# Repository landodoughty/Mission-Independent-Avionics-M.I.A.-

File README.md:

# Mission-Independent-Avionics-M.I.A.-
My Custom Rocket Avionics System

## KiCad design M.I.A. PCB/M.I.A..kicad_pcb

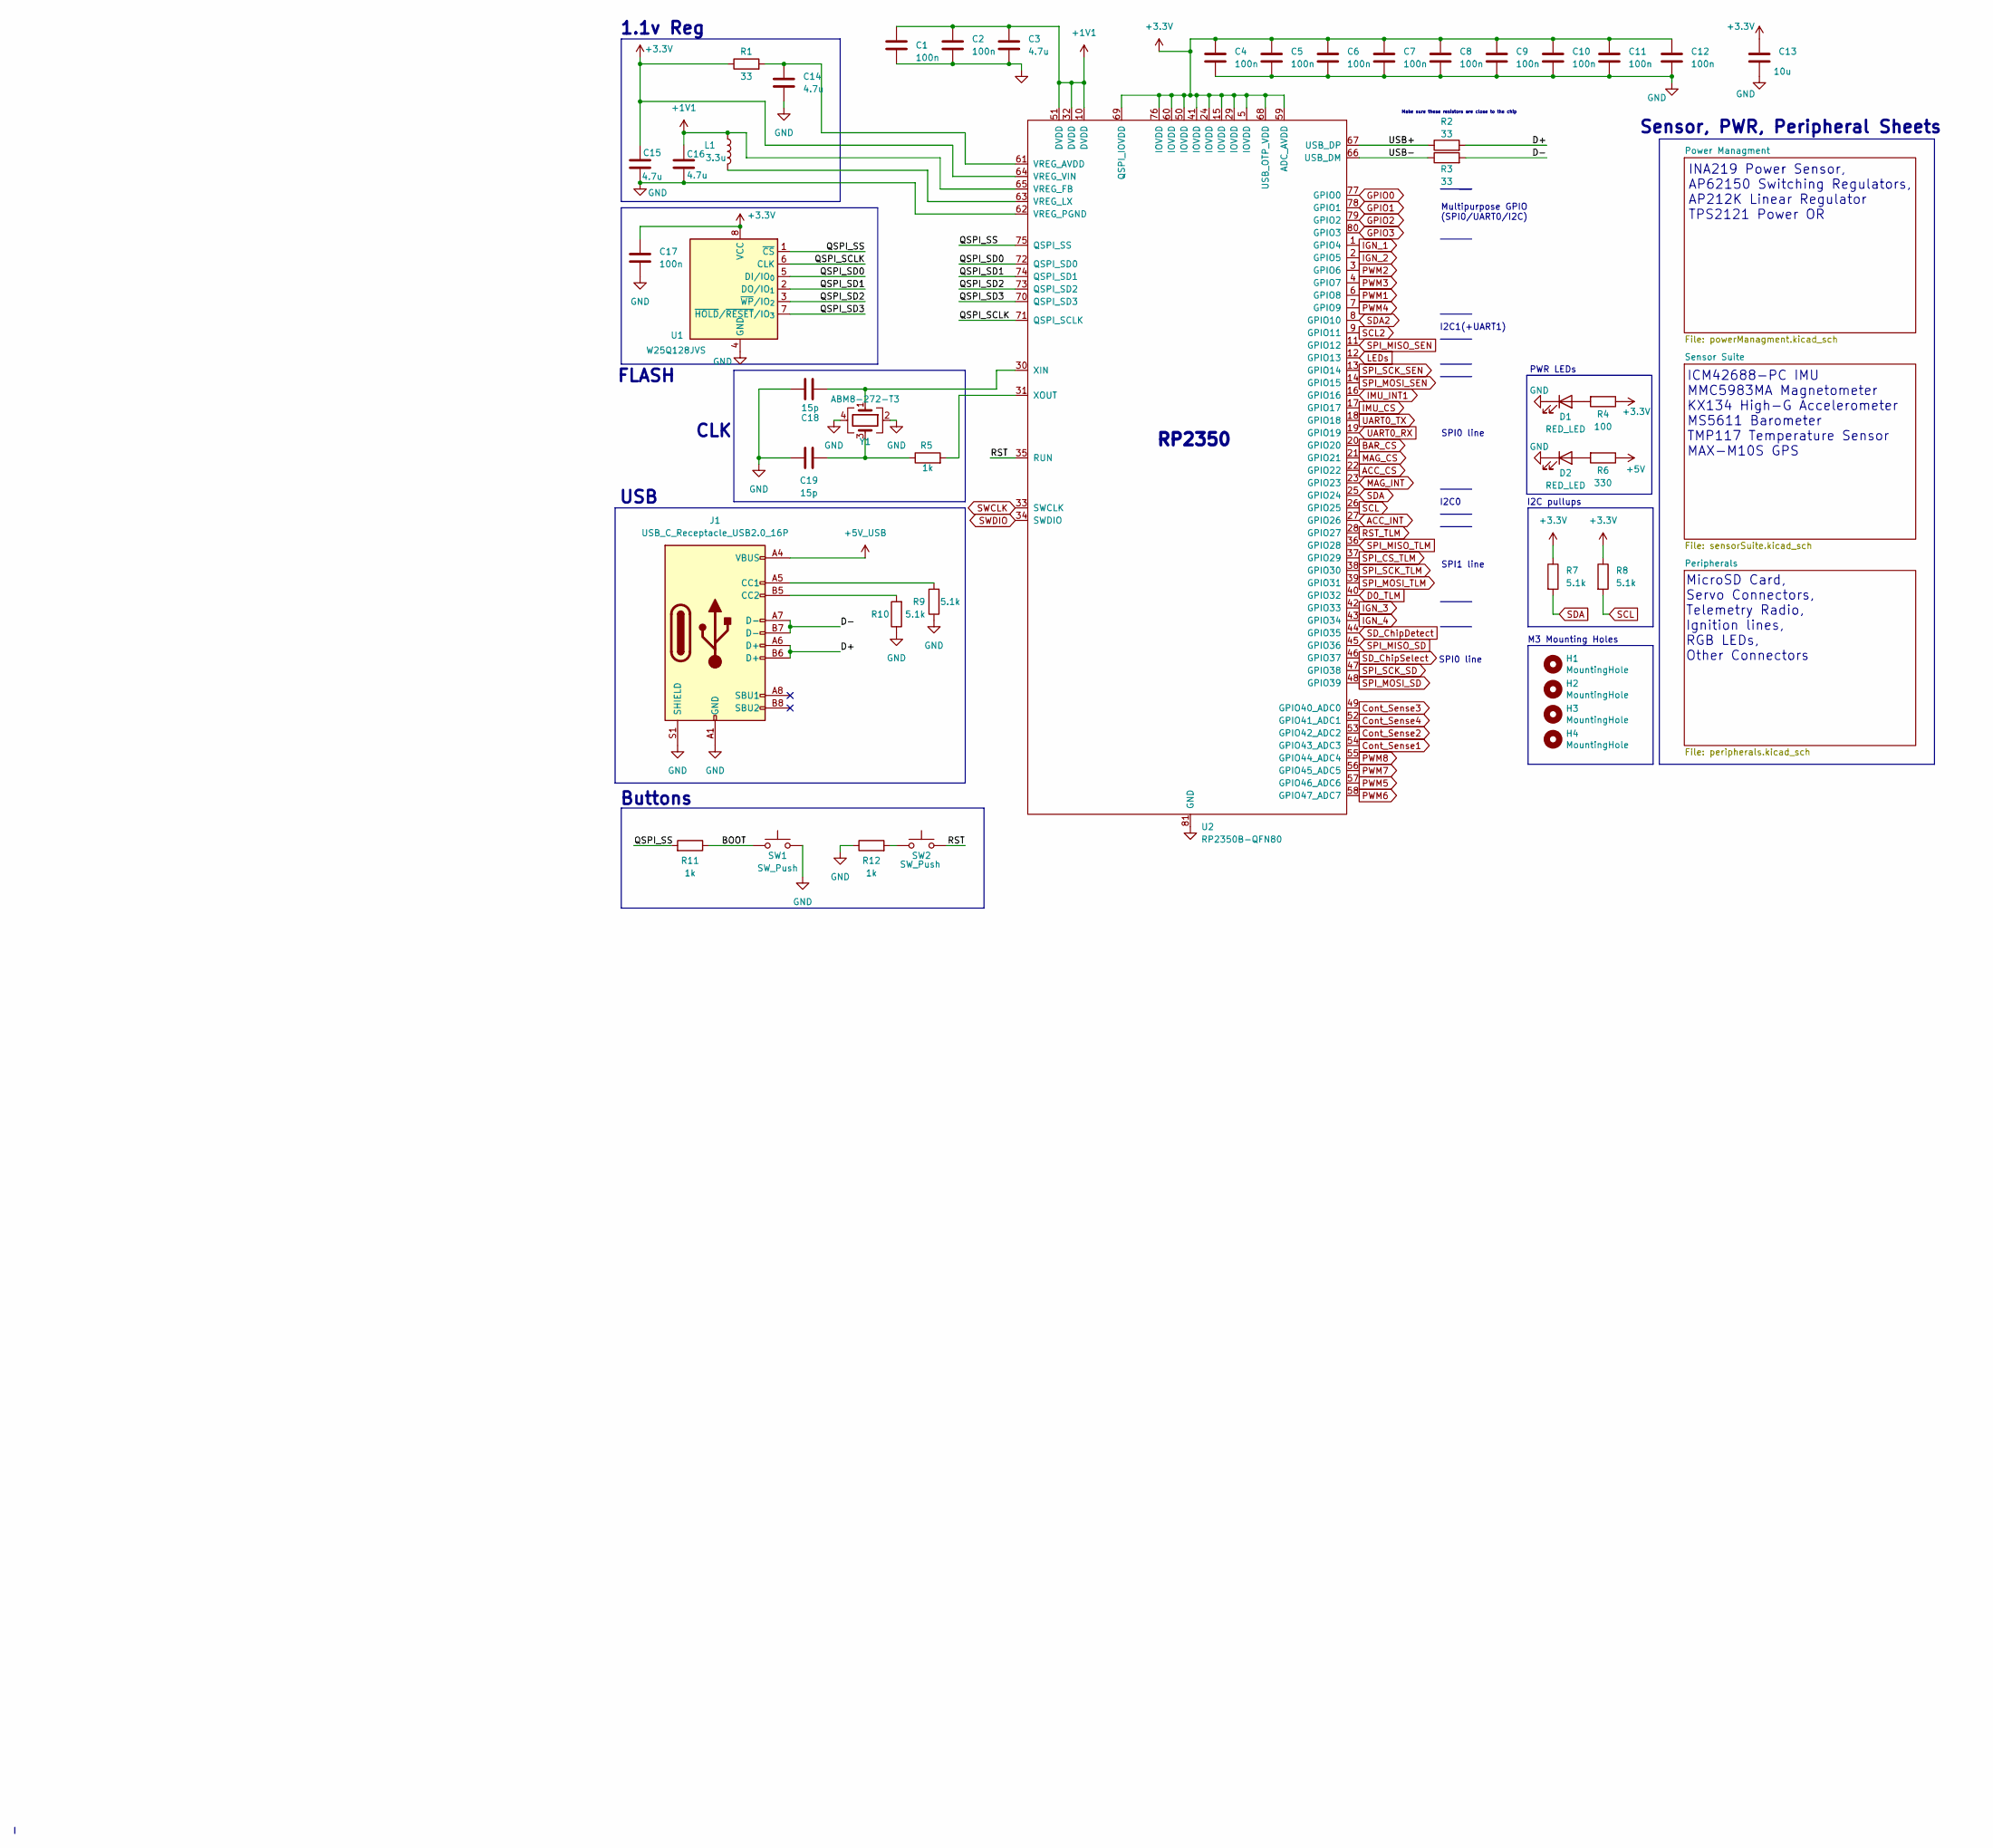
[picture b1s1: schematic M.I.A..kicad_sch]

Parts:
C1, C2, C4, C5, C6, C7, C8, C9, C10, C11, C12, C17: 100n; C_0603_1608Metric; LCSC Part Number C1525
C3, C14, C15, C16: 4.7u; C_0805_2012Metric; LCSC Part Number C23733
C13: 10u; C_0805_2012Metric; LCSC Part Number C15850
C18, C19: 15p; C_0603_1608Metric; LCSC Part Number C1548
D1, D2: RED_LED; LED_0805_2012Metric; LCSC Part Number C84256
H1, H2, H3, H4: MountingHole; MountingHole_3.2mm_M3_ISO14580_Pad
J1: USB_C_Receptacle_USB2.0_16P; USB_C_Receptacle_HRO_TYPE-C-31-M-12
L1: 3.3u; AOTA-B201610S3R3-101-T(L_0806_2016metric)
R1: 33; R_0603_1608Metric; LCSC Part Number C25105
R2, R3: 33; R_0603_1608Metric; LCSC Part Number C25092
R4: 100; R_0603_1608Metric; LCSC Part Number C25076
R5, R11, R12: 1k; R_0603_1608Metric; LCSC Part Number C11702
R6: 330; R_0603_1608Metric; LCSC Part Number C25076
R7, R8: 5.1k; R_0603_1608Metric; LCSC Part Number C25900
R9, R10: 5.1k; R_0603_1608Metric; LCSC Part Number C25105
SW1, SW2: SW_Push; SW_Push_SPST_NO_Alps_SKRK
U1: W25Q128JVS; WSON-8-1EP_6x5mm_P1.27mm_EP3.4x4mm; LCSC Part Number C97521
U2: RP2350B-QFN80; QFN-80-1EP_10x10mm_P0.4mm_EP3.4x3.4mm
Y1: ABM8-272-T3; Crystal_SMD_3225-4Pin_3.2x2.5mm; LCSC Part Number C20625731

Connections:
+1V1: C1.1, C2.1, C3.1, C16.1, L1.1, U2.10 (DVDD), U2.32 (DVDD), U2.51 (DVDD), U2.65 (VREG_FB)
+3.3V: C4.1, C5.1, C6.1, C7.1, C8.1, C9.1, C10.1, C11.1, C12.1, C13.1, C15.1, C17.1, R1.1, R4.1, R7.1, R8.1, U1.8 (VCC), U2.5 (IOVDD), U2.15 (IOVDD), U2.24 (IOVDD), U2.29 (IOVDD), U2.41 (IOVDD), U2.50 (IOVDD), U2.59 (ADC_AVDD), U2.60 (IOVDD), U2.64 (VREG_VIN), U2.68 (USB_OTP_VDD), U2.69 (QSPI_IOVDD), U2.76 (IOVDD); also elsewhere on the board
+5V: R6.1; also elsewhere on the board
+5V_USB: J1.A4 (VBUS), J1.A9 (VBUS), J1.B4 (VBUS), J1.B9 (VBUS); also elsewhere on the board
/BOOT: R11.1, SW1.2
/D+: J1.A6 (D+), J1.B6 (D+), R2.2
/D-: J1.A7 (D-), J1.B7 (D-), R3.2
/QSPI_SCLK: U1.6 (CLK), U2.71 (QSPI_SCLK)
/QSPI_SD0: U1.5 (DI/IO_{0}), U2.72 (QSPI_SD0)
/QSPI_SD1: U1.2 (DO/IO_{1}), U2.74 (QSPI_SD1)
/QSPI_SD2: U1.3 (~WP/IO_{2}), U2.73 (QSPI_SD2)
/QSPI_SD3: U1.7 (~HOLD/~RESET/IO_{3}), U2.70 (QSPI_SD3)
/QSPI_SS: R11.2, U1.1 (~CS), U2.75 (QSPI_SS)
/RST: SW2.2, U2.35 (RUN)
/USB+: R2.1, U2.67 (USB_DP)
/USB-: R3.1, U2.66 (USB_DM)
ACC_CS: U2.22 (GPIO22); also elsewhere on the board
ACC_INT: U2.27 (GPIO26); also elsewhere on the board
BAR_CS: U2.20 (GPIO20); also elsewhere on the board
Cont_Sense1: U2.54 (GPIO43_ADC3); also elsewhere on the board
Cont_Sense2: U2.53 (GPIO42_ADC2); also elsewhere on the board
Cont_Sense3: U2.49 (GPIO40_ADC0); also elsewhere on the board
Cont_Sense4: U2.52 (GPIO41_ADC1); also elsewhere on the board
D0_TLM: U2.40 (GPIO32); also elsewhere on the board
GND: C1.2, C2.2, C3.2, C4.2, C5.2, C6.2, C7.2, C8.2, C9.2, C10.2, C11.2, C12.2, C13.2, C14.2, C15.2, C16.2, C17.2, C18.1, C19.1, D1.1 (K), D2.1 (K), J1.A1 (GND), J1.A12 (GND), J1.B1 (GND), J1.B12 (GND), J1.S1 (SHIELD), R9.1, R10.1, R12.1, SW1.1, U1.4 (GND), U2.62 (VREG_PGND), U2.81 (GND), Y1.2, Y1.4; also elsewhere on the board
GPIO0: U2.77 (GPIO0); also elsewhere on the board
GPIO1: U2.78 (GPIO1); also elsewhere on the board
GPIO2: U2.79 (GPIO2); also elsewhere on the board
GPIO3: U2.80 (GPIO3); also elsewhere on the board
IGN_1: U2.1 (GPIO4); also elsewhere on the board
IGN_2: U2.2 (GPIO5); also elsewhere on the board
IGN_3: U2.42 (GPIO33); also elsewhere on the board
IGN_4: U2.43 (GPIO34); also elsewhere on the board
IMU_CS: U2.17 (GPIO17); also elsewhere on the board
IMU_INT1: U2.16 (GPIO16); also elsewhere on the board
LEDs: U2.12 (GPIO13); also elsewhere on the board
MAG_CS: U2.21 (GPIO21); also elsewhere on the board
MAG_INT: U2.23 (GPIO23); also elsewhere on the board
unnamed: C19.2, R5.1, Y1.3
unnamed: D1.2 (A), R4.2
unnamed: D2.2 (A), R6.2
unnamed: J1.A5 (CC1), R9.2
unnamed: J1.B5 (CC2), R10.2
unnamed: R12.2, SW2.1
unnamed: C14.1, R1.2, U2.61 (VREG_AVDD)
unnamed: L1.2, U2.63 (VREG_LX)
unnamed: C18.2, U2.30 (XIN), Y1.1
unnamed: R5.2, U2.31 (XOUT)
PWM1: U2.6 (GPIO8); also elsewhere on the board
PWM2: U2.3 (GPIO6); also elsewhere on the board
PWM3: U2.4 (GPIO7); also elsewhere on the board
PWM4: U2.7 (GPIO9); also elsewhere on the board
PWM5: U2.57 (GPIO46_ADC6); also elsewhere on the board
PWM6: U2.58 (GPIO47_ADC7); also elsewhere on the board
PWM7: U2.56 (GPIO45_ADC5); also elsewhere on the board
PWM8: U2.55 (GPIO44_ADC4); also elsewhere on the board
RST_TLM: U2.28 (GPIO27); also elsewhere on the board
SCL: R8.2, U2.26 (GPIO25); also elsewhere on the board
SCL2: U2.9 (GPIO11); also elsewhere on the board
SDA: R7.2, U2.25 (GPIO24); also elsewhere on the board
SDA2: U2.8 (GPIO10); also elsewhere on the board
SD_ChipDetect: U2.44 (GPIO35); also elsewhere on the board
SD_ChipSelect: U2.46 (GPIO37); also elsewhere on the board
SPI_CS_TLM: U2.37 (GPIO29); also elsewhere on the board
SPI_MISO_SD: U2.45 (GPIO36); also elsewhere on the board
SPI_MISO_SEN: U2.11 (GPIO12); also elsewhere on the board
SPI_MISO_TLM: U2.36 (GPIO28); also elsewhere on the board
SPI_MOSI_SD: U2.48 (GPIO39); also elsewhere on the board
SPI_MOSI_SEN: U2.14 (GPIO15); also elsewhere on the board
SPI_MOSI_TLM: U2.39 (GPIO31); also elsewhere on the board
SPI_SCK_SD: U2.47 (GPIO38); also elsewhere on the board
SPI_SCK_SEN: U2.13 (GPIO14); also elsewhere on the board
SPI_SCK_TLM: U2.38 (GPIO30); also elsewhere on the board
SWCLK: U2.33 (SWCLK); also elsewhere on the board
SWDIO: U2.34 (SWDIO); also elsewhere on the board
UART0_RX: U2.19 (GPIO19); also elsewhere on the board
UART0_TX: U2.18 (GPIO18); also elsewhere on the board

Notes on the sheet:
FLASH
Buttons
I2C0
I2C1(+UART1)
I2C pullups
SPI0 line
SPI1 line
MicroSD Card, Servo Connectors, Telemetry Radio, Ignition lines, RGB LEDs, Other Connectors
Make sure these resistors are close to the chip
USB
ICM42688-PC IMU MMC5983MA Magnetometer KX134 High-G Accelerometer MS5611 Barometer TMP117 Temperature Sensor MAX-M10S GPS
Multipurpose GPIO (SPI0/UART0/I2C)
1.1v Reg
INA219 Power Sensor, AP62150 Switching Regulators, AP212K Linear Regulator TPS2121 Power OR
CLK
PWR LEDs
RP2350
M3 Mounting Holes
Sensor, PWR, Peripheral Sheets

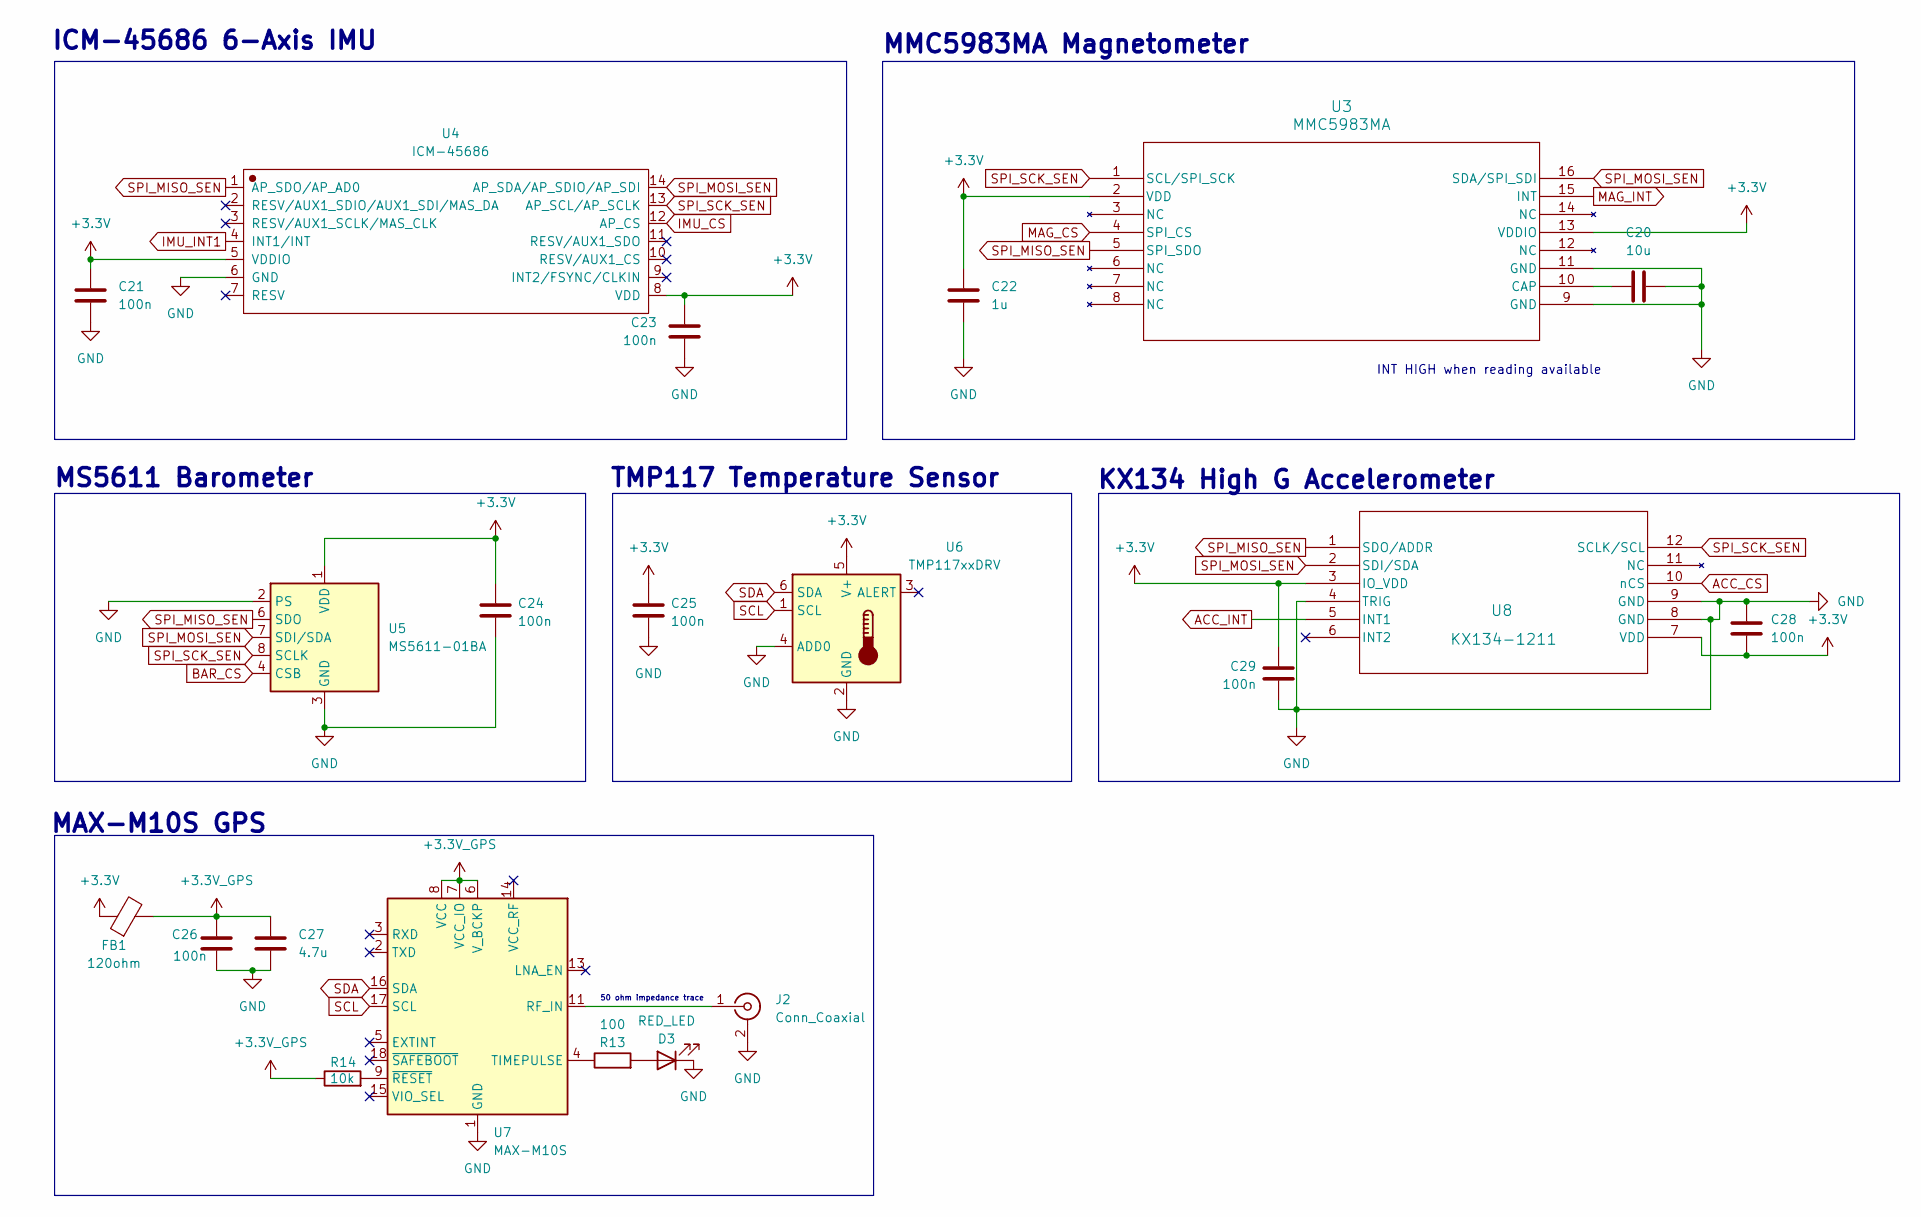
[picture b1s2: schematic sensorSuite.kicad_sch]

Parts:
C20: 10u; C_0805_2012Metric; LCSC Part Number C15850
C21, C23, C24, C25, C26, C28, C29: 100n; C_0603_1608Metric; LCSC Part Number C1525
C22: 1u; C_0805_2012Metric; LCSC Part Number C28323
C27: 4.7u; C_0805_2012Metric; LCSC Part Number C23733
D3: RED_LED; LED_0805_2012Metric; LCSC Part Number C84256
FB1: 120ohm; L_0805_2012Metric
J2: Conn_Coaxial; SMA_Amphenol_132134-11_Vertical
R13: 100; R_0603_1608Metric; LCSC Part Number C25076
R14: 10k; R_0603_1608Metric; LCSC Part Number C25744
U3: MMC5983MA; LGA-16_3x3mm_P0.5mm; LCSC Part Number C404329
U4: ICM-45686; Bosch_LGA-14_3x2.5mm_P0.5mm; Manufacturer Part ICM-45686; LCSC C22459454
U5: MS5611-01BA; LGA-8_3x5mm_P1.25mm; LCSC Part Number C15639
U6: TMP117xxDRV; WSON-6-1EP_2x2mm_P0.65mm_EP1x1.6mm
U7: MAX-M10S; ublox_MAX
U8: KX134-1211; LGA-12_2x2mm_P0.5mm; LCSC Part Number C2157908

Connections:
+3.3V: C21.1, C22.2, C23.1, C24.1, C25.1, C28.2, C29.1, FB1.1, U3.2 (VDD), U3.13 (VDDIO), U4.5 (VDDIO), U4.8 (VDD), U5.1 (VDD), U6.5 (V+), U8.3 (IO_VDD), U8.7 (VDD); also elsewhere on the board
+3.3V_GPS: C26.1, C27.1, FB1.2, R14.1, U7.6 (V_BCKP), U7.7 (VCC_IO), U7.8 (VCC)
ACC_CS: U8.10 (nCS); also elsewhere on the board
ACC_INT: U8.5 (INT1); also elsewhere on the board
BAR_CS: U5.4 (CSB), U5.5 (CSB); also elsewhere on the board
GND: C20.2, C21.2, C22.1, C23.2, C24.2, C25.2, C26.2, C27.2, C28.1, C29.2, D3.1 (K), J2.2 (Ext), U3.9 (GND), U3.11 (GND), U4.6 (GND), U5.2 (PS), U5.3 (GND), U6.2 (GND), U6.4 (ADD0), U7.1 (GND), U7.10 (GND), U7.12 (GND), U8.4 (TRIG), U8.8 (GND), U8.9 (GND); also elsewhere on the board
IMU_CS: U4.12 (AP_CS); also elsewhere on the board
IMU_INT1: U4.4 (INT1/INT); also elsewhere on the board
MAG_CS: U3.4 (SPI_CS); also elsewhere on the board
MAG_INT: U3.15 (INT); also elsewhere on the board
unnamed: D3.2 (A), R13.2
unnamed: J2.1 (In), U7.11 (RF_IN)
unnamed: C20.1, U3.10 (CAP)
unnamed: R13.1, U7.4 (TIMEPULSE)
unnamed: R14.2, U7.9 (~RESET)
SCL: U6.1 (SCL), U7.17 (SCL); also elsewhere on the board
SDA: U6.6 (SDA), U7.16 (SDA); also elsewhere on the board
SPI_MISO_SEN: U3.5 (SPI_SDO), U4.1 (AP_SDO/AP_AD0), U5.6 (SDO), U8.1 (SDO/ADDR); also elsewhere on the board
SPI_MOSI_SEN: U3.16 (SDA/SPI_SDI), U4.14 (AP_SDA/AP_SDIO/AP_SDI), U5.7 (SDI/SDA), U8.2 (SDI/SDA); also elsewhere on the board
SPI_SCK_SEN: U3.1 (SCL/SPI_SCK), U4.13 (AP_SCL/AP_SCLK), U5.8 (SCLK), U8.12 (SCLK/SCL); also elsewhere on the board

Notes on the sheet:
MMC5983MA Magnetometer
MS5611 Barometer
INT HIGH when reading available
ICM-45686 6-Axis IMU
TMP117 Temperature Sensor
KX134 High G Accelerometer
MAX-M10S GPS
50 ohm impedance trace

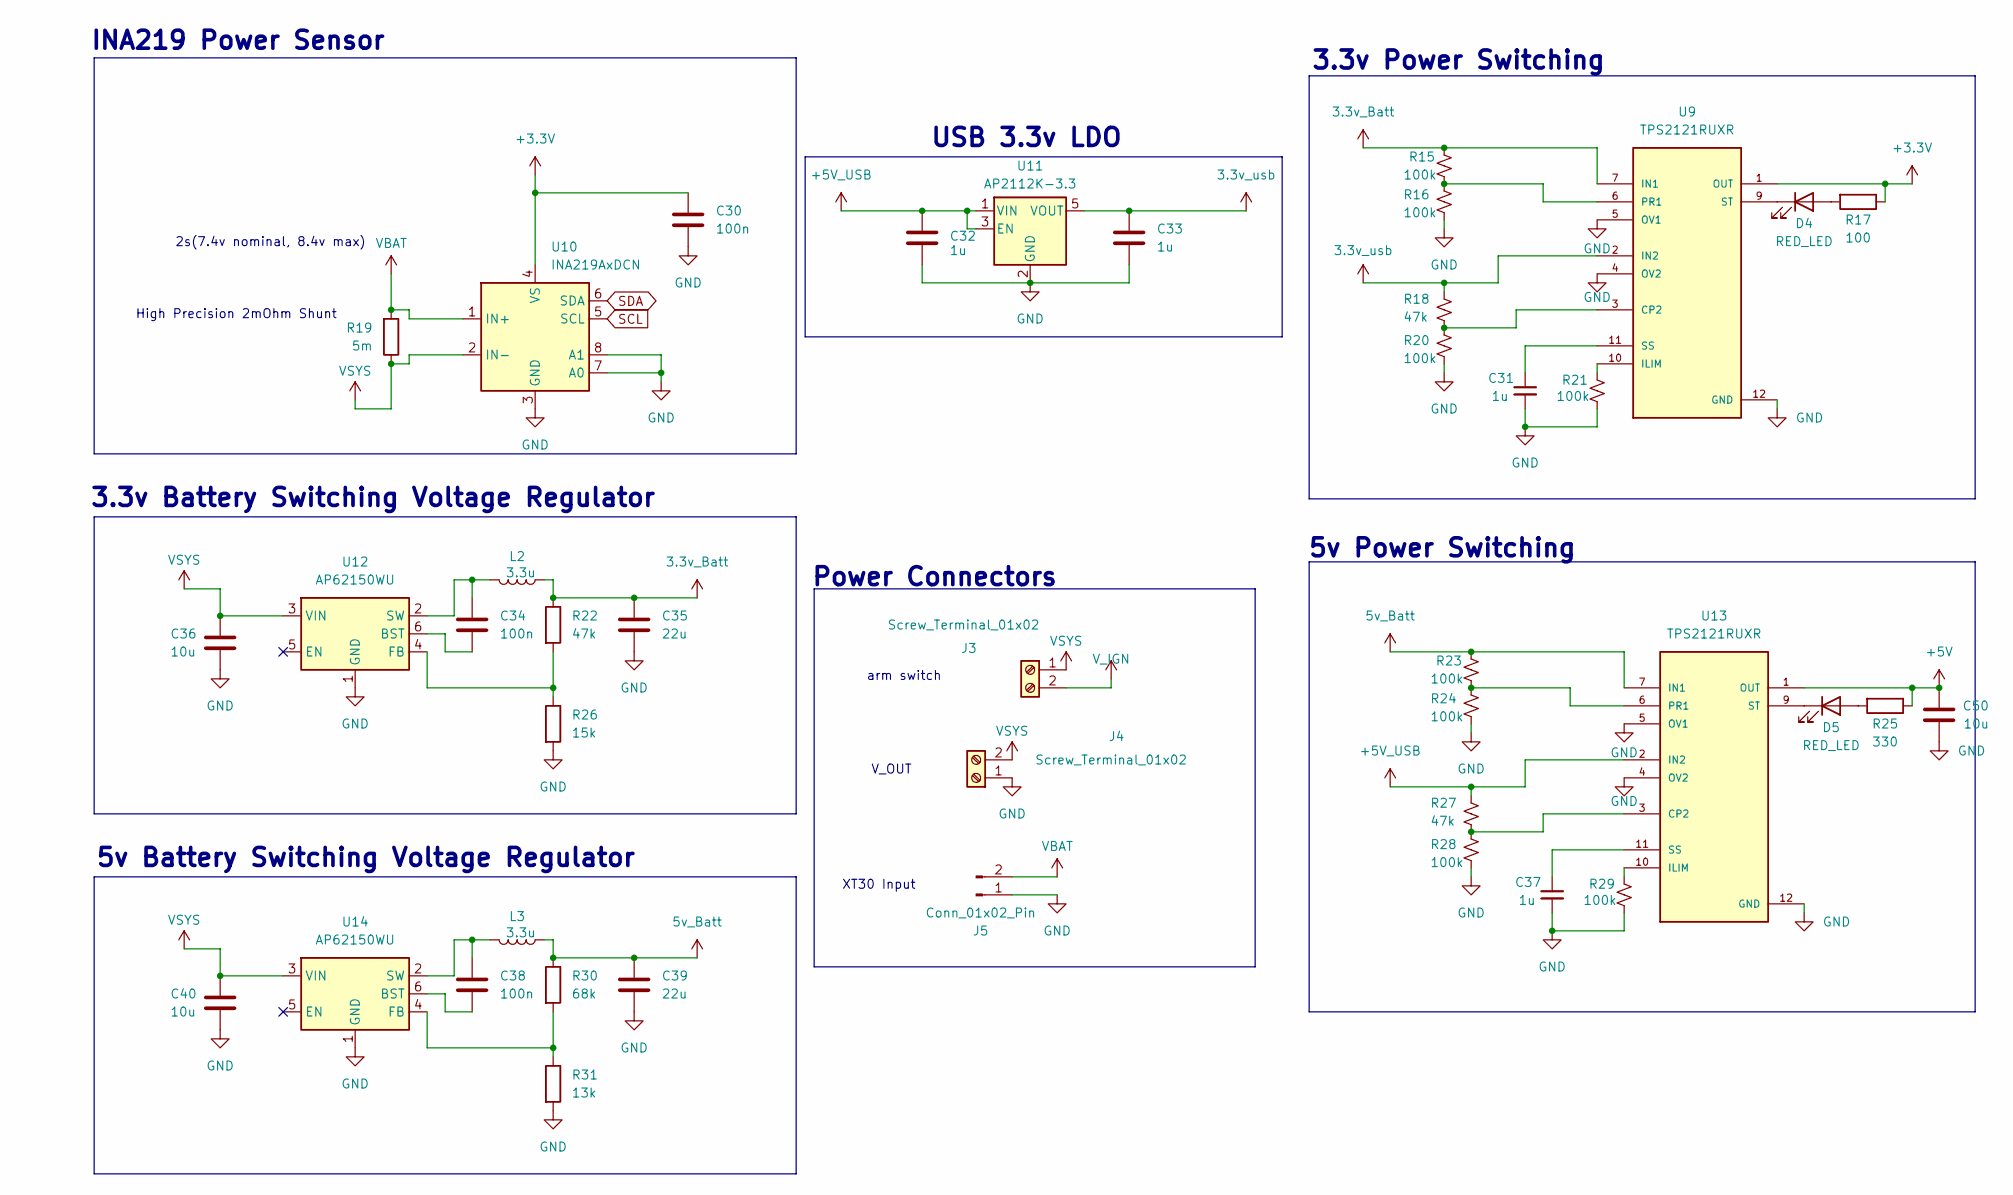
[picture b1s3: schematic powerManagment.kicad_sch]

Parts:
C30, C34, C38: 100n; C_0603_1608Metric; LCSC Part Number C1525
C31, C37: 1u; C_0805_2012Metric; LCSC Part Number C28323
C32, C33: 1u; C_0805_2012Metric; LCSC Part Number C15850
C35, C39: 22u; C_0805_2012Metric; LCSC Part Number C45783
C36, C40, C50: 10u; C_0805_2012Metric; JLCPCB Part # C15850
D4, D5: RED_LED; LED_0805_2012Metric; LCSC Part Number C84256
J3, J4: Screw_Terminal_01x02; ScrewTerminal_1x02_P3.5mm_Horizontal_Black
J5: Conn_01x02_Pin; AMASS_XT30PW-M_1x02_P2.50mm_Horizontal
L2, L3: 3.3u; AOTA-B201610S3R3-101-T(L_0806_2016metric)
R15, R23: 100k; R_0603_1608Metric; LCSC Part Number C25792
R16, R20, R21, R24, R28, R29: 100k; R_0603_1608Metric; LCSC Part Number C25741
R17: 100; R_0603_1608Metric; LCSC Part Number C25076
R18, R27: 47k; R_0603_1608Metric; LCSC Part Number C25741
R19: 5m; R_1206_3216Metric
R22: 47k; R_0603_1608Metric; LCSC Part Number C25792
R25: 330; R_0603_1608Metric; LCSC Part Number C25076
R26: 15k; R_0603_1608Metric; LCSC Part Number C25756
R30: 68k; R_0603_1608Metric; LCSC Part Number C25792
R31: 13k; R_0603_1608Metric; LCSC Part Number C25756
U9, U13: TPS2121RUXR; Texas_VQFN-HR-12_2x2.5mm_P0.5mm; LCSC Part Number C485916
U10: INA219AxDCN; SOT-23-8
U11: AP2112K-3.3; SOT-23-5
U12, U14: AP62150WU; TSOT-23-6; LCSC Part Number C3194237

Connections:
3.3v_Batt: C35.1, L2.1, R15.1, R22.1, U9.7 (IN1)
3.3v_usb: C33.1, R18.1, U9.2 (IN2), U11.5 (VOUT)
5v_Batt: C39.1, L3.1, R23.1, R30.1, U13.7 (IN1)
+3.3V: C30.1, R17.1, U9.1 (OUT), U9.8 (OUT), U10.4 (VS); also elsewhere on the board
+5V: C50.1, R25.1, U13.1 (OUT), U13.8 (OUT); also elsewhere on the board
+5V_USB: C32.1, R27.1, U11.1 (VIN), U11.3 (EN), U13.2 (IN2); also elsewhere on the board
GND: C30.2, C31.2, C32.2, C33.2, C35.2, C36.2, C37.2, C39.2, C40.2, C50.2, J4.1, J5.1, R16.2, R20.2, R21.2, R24.2, R26.2, R28.2, R29.2, R31.2, U9.4 (OV2), U9.5 (OV1), U9.12 (GND), U10.3 (GND), U10.7 (A0), U10.8 (A1), U11.2 (GND), U12.1 (GND), U13.4 (OV2), U13.5 (OV1), U13.12 (GND), U14.1 (GND); also elsewhere on the board
unnamed: D4.2 (A), R17.2
unnamed: D4.1 (K), U9.9 (ST)
unnamed: D5.2 (A), R25.2
unnamed: D5.1 (K), U13.9 (ST)
unnamed: R18.2, R20.1, U9.3 (CP2)
unnamed: R21.1, U9.10 (ILIM)
unnamed: R15.2, R16.1, U9.6 (PR1)
unnamed: C31.1, U9.11 (SS)
unnamed: C34.2, U12.6 (BST)
unnamed: R22.2, R26.1, U12.4 (FB)
unnamed: C34.1, L2.2, U12.2 (SW)
unnamed: R27.2, R28.1, U13.3 (CP2)
unnamed: R29.1, U13.10 (ILIM)
unnamed: R23.2, R24.1, U13.6 (PR1)
unnamed: C37.1, U13.11 (SS)
unnamed: C38.2, U14.6 (BST)
unnamed: R30.2, R31.1, U14.4 (FB)
unnamed: C38.1, L3.2, U14.2 (SW)
SCL: U10.5 (SCL); also elsewhere on the board
SDA: U10.6 (SDA); also elsewhere on the board
VBAT: J5.2, R19.2, U10.1 (IN+)
VSYS: C36.1, C40.1, J3.1, J4.2, R19.1, U10.2 (IN-), U12.3 (VIN), U14.3 (VIN); also elsewhere on the board
V_IGN: J3.2; also elsewhere on the board

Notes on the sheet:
Power Connectors
3.3v Battery Switching Voltage Regulator
5v Power Switching
arm switch
3.3v Power Switching
V_OUT
INA219 Power Sensor
XT30 Input
5v Battery Switching Voltage Regulator
2s(7.4v nominal, 8.4v max)
USB 3.3v LDO
High Precision 2mOhm Shunt

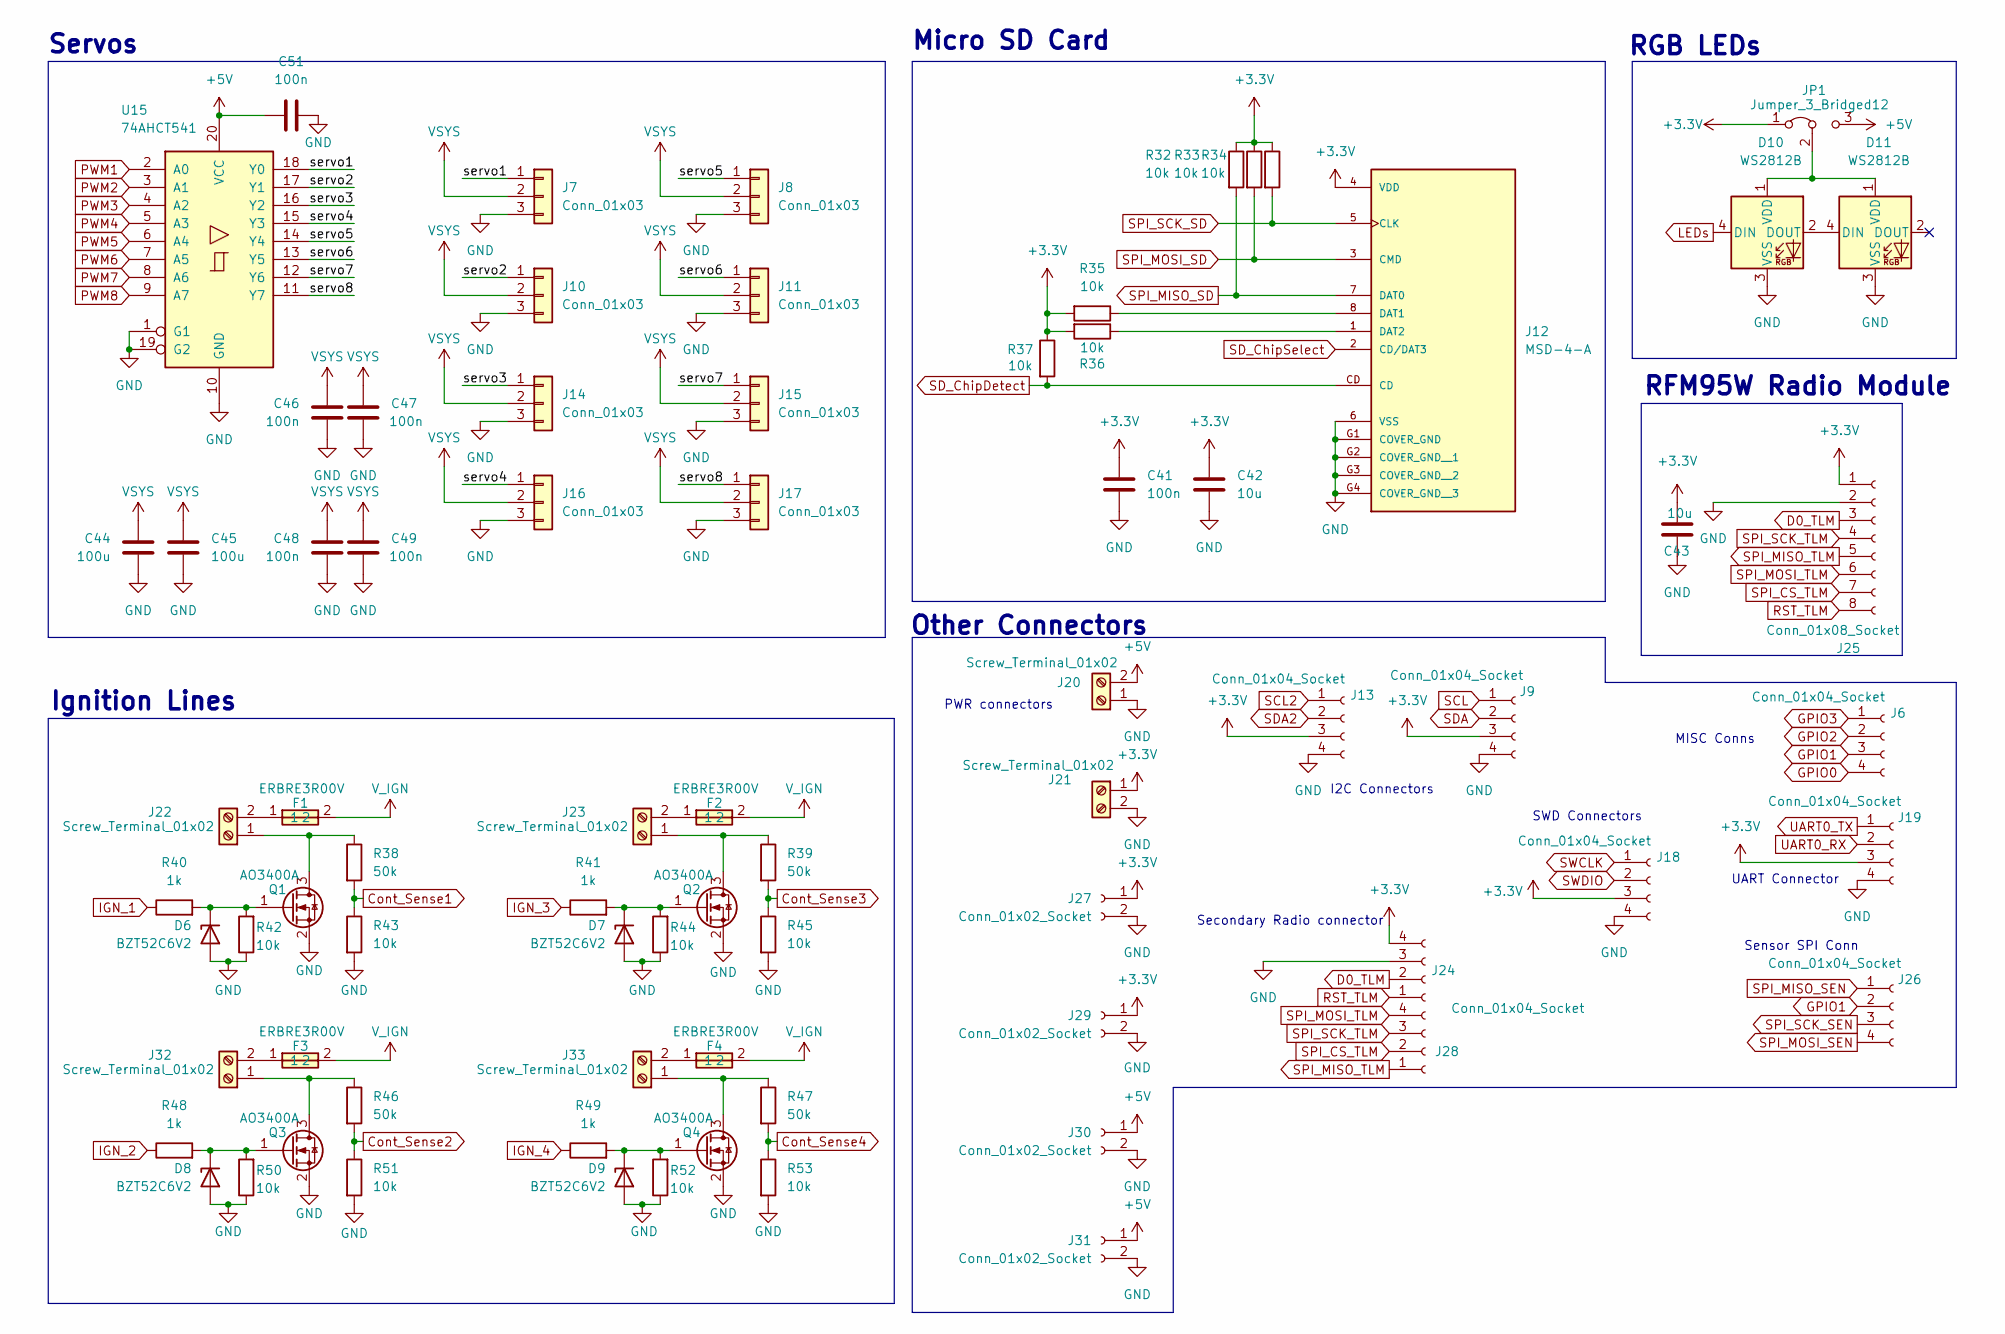
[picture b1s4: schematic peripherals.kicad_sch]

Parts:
C41, C51: 100n; C_0603_1608Metric; LCSC Part Number C1525
C42: 10u; C_0805_2012Metric; LCSC Part Number C15850
C43: 10u; C_0805_2012Metric
C44, C45: 100u; C_Radial_D5.0mm_H11.0mm_P2.00mm; LCSC Part Number C15850
C46, C47, C48, C49: 100n; C_0603_1608Metric; LCSC Part Number C15850
D6, D7, D8, D9: BZT52C6V2; D_SOD-123F
D10, D11: WS2812B; LED_WS2812B_PLCC4_5.0x5.0mm_P3.2mm
F1, F2, F3, F4: ERBRE3R00V; Manufacturer Part ERBRE3R00V; LCSC C713406
J6, J9, J13, J18, J19, J24, J26, J28: Conn_01x04_Socket; JST_PH_B4B-PH-K_1x04_P2.00mm_Vertical
J7, J8, J10, J11, J14, J15, J16, J17: Conn_01x03; PinHeader_1x03_P2.54mm_Vertical
J12: MSD-4-A; CUI_MSD-4-A; PARTREV 1.0
J20, J21, J22, J23, J32, J33: Screw_Terminal_01x02; ScrewTerminal_1x02_P3.5mm_Horizontal_Black
J25: Conn_01x08_Socket; JST_SHL_SM08B-SHLS-TF_1x08-1MP_P1.00mm_Horizontal
J27, J29, J30, J31: Conn_01x02_Socket; JST_PH_B2B-PH-K_1x02_P2.00mm_Vertical
JP1: Jumper_3_Bridged12; SolderJumper-3_P1.3mm_Bridged12_RoundedPad1.0x1.5mm_NumberL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
Q1, Q2, Q3, Q4: AO3400A; SOT-23
R32, R33, R34, R35, R36, R37: 10k; R_0603_1608Metric; LCSC Part Number C25744
R38, R39, R46, R47: 50k; R_0603_1608Metric
R40, R41, R48, R49: 1k; R_0603_1608Metric
R42, R43, R44, R45, R50, R51, R52, R53: 10k; R_0603_1608Metric
U15: 74AHCT541; SSOP-20_4.4x6.5mm_P0.65mm

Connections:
+3.3V: C41.1, C42.1, C43.1, J9.3, J12.4 (VDD), J13.3, J18.3, J19.3, J21.1, J24.4, J25.1, J27.1, J29.1, JP1.1 (A), R32.1, R33.1, R34.1, R35.2, R36.2, R37.1; also elsewhere on the board
+5V: C51.1, J20.2, J30.1, J31.1, JP1.3 (B), U15.20 (VCC); also elsewhere on the board
/Peripherals/servo1: J7.1, U15.18 (Y0)
/Peripherals/servo2: J10.1, U15.17 (Y1)
/Peripherals/servo3: J14.1, U15.16 (Y2)
/Peripherals/servo4: J16.1, U15.15 (Y3)
/Peripherals/servo5: J8.1, U15.14 (Y4)
/Peripherals/servo6: J11.1, U15.13 (Y5)
/Peripherals/servo7: J15.1, U15.12 (Y6)
/Peripherals/servo8: J17.1, U15.11 (Y7)
Cont_Sense1: R38.2, R43.1; also elsewhere on the board
Cont_Sense2: R46.2, R51.1; also elsewhere on the board
Cont_Sense3: R39.2, R45.1; also elsewhere on the board
Cont_Sense4: R47.2, R53.1; also elsewhere on the board
D0_TLM: J24.2, J25.3; also elsewhere on the board
GND: C41.2, C42.2, C43.2, C44.2, C45.2, C46.2, C47.2, C48.2, C49.2, C51.2, D6.2 (A), D7.2 (A), D8.2 (A), D9.2 (A), D10.3 (VSS), D11.3 (VSS), J7.3, J8.3, J9.4, J10.3, J11.3, J12.6 (VSS), J12.G1 (COVER_GND), J12.G2 (COVER_GND__1), J12.G3 (COVER_GND__2), J12.G4 (COVER_GND__3), J13.4, J14.3, J15.3, J16.3, J17.3, J18.4, J19.4, J20.1, J21.2, J24.3, J25.2, J27.2, J29.2, J30.2, J31.2, Q1.2 (S), Q2.2 (S), Q3.2 (S), Q4.2 (S), R42.1, R43.2, R44.1, R45.2, R50.1, R51.2, R52.1, R53.2, U15.1 (G1), U15.10 (GND), U15.19 (G2); also elsewhere on the board
GPIO0: J6.4; also elsewhere on the board
GPIO1: J6.3, J26.2; also elsewhere on the board
GPIO2: J6.2; also elsewhere on the board
GPIO3: J6.1; also elsewhere on the board
IGN_1: R40.1; also elsewhere on the board
IGN_2: R48.1; also elsewhere on the board
IGN_3: R41.1; also elsewhere on the board
IGN_4: R49.1; also elsewhere on the board
LEDs: D10.4 (DIN); also elsewhere on the board
unnamed: D6.1 (K), Q1.1 (G), R40.2, R42.2
unnamed: D7.1 (K), Q2.1 (G), R41.2, R44.2
unnamed: D8.1 (K), Q3.1 (G), R48.2, R50.2
unnamed: D9.1 (K), Q4.1 (G), R49.2, R52.2
unnamed: D10.2 (DOUT), D11.4 (DIN)
unnamed: D10.1 (VDD), D11.1 (VDD), JP1.2 (C)
unnamed: J12.8 (DAT1), R35.1
unnamed: J12.1 (DAT2), R36.1
unnamed: J22.1, Q1.3 (D), R38.1
unnamed: F1.1, J22.2
unnamed: J23.1, Q2.3 (D), R39.1
unnamed: F2.1, J23.2
unnamed: J32.1, Q3.3 (D), R46.1
unnamed: F3.1, J32.2
unnamed: J33.1, Q4.3 (D), R47.1
unnamed: F4.1, J33.2
PWM1: U15.2 (A0); also elsewhere on the board
PWM2: U15.3 (A1); also elsewhere on the board
PWM3: U15.4 (A2); also elsewhere on the board
PWM4: U15.5 (A3); also elsewhere on the board
PWM5: U15.6 (A4); also elsewhere on the board
PWM6: U15.7 (A5); also elsewhere on the board
PWM7: U15.8 (A6); also elsewhere on the board
PWM8: U15.9 (A7); also elsewhere on the board
RST_TLM: J24.1, J25.8; also elsewhere on the board
SCL: J9.1; also elsewhere on the board
SCL2: J13.1; also elsewhere on the board
SDA: J9.2; also elsewhere on the board
SDA2: J13.2; also elsewhere on the board
SD_ChipDetect: J12.CD, R37.2; also elsewhere on the board
SD_ChipSelect: J12.2 (CD/DAT3); also elsewhere on the board
SPI_CS_TLM: J25.7, J28.2; also elsewhere on the board
SPI_MISO_SD: J12.7 (DAT0), R32.2; also elsewhere on the board
SPI_MISO_SEN: J26.1; also elsewhere on the board
SPI_MISO_TLM: J25.5, J28.1; also elsewhere on the board
SPI_MOSI_SD: J12.3 (CMD), R33.2; also elsewhere on the board
SPI_MOSI_SEN: J26.4; also elsewhere on the board
SPI_MOSI_TLM: J25.6, J28.4; also elsewhere on the board
SPI_SCK_SD: J12.5 (CLK), R34.2; also elsewhere on the board
SPI_SCK_SEN: J26.3; also elsewhere on the board
SPI_SCK_TLM: J25.4, J28.3; also elsewhere on the board
SWCLK: J18.1; also elsewhere on the board
SWDIO: J18.2; also elsewhere on the board
UART0_RX: J19.2; also elsewhere on the board
UART0_TX: J19.1; also elsewhere on the board
VSYS: C44.1, C45.1, C46.1, C47.1, C48.1, C49.1, J7.2, J8.2, J10.2, J11.2, J14.2, J15.2, J16.2, J17.2; also elsewhere on the board
V_IGN: F1.2, F2.2, F3.2, F4.2; also elsewhere on the board

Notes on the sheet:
Servos
UART Connector
Sensor SPI Conn
RGB LEDs
SWD Connectors
MISC Conns
I2C Connectors
Ignition Lines
PWR connectors
Other Connectors
Micro SD Card
RFM95W Radio Module
Secondary Radio connector
